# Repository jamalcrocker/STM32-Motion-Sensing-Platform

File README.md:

# STM32 Inertial Sensing PCB

### Custom 4-Layer Embedded Hardware Design | KiCad | STM32L476 | MPU-6050

**Project Status:** In Progress — PCB Design and Layout

## Project Overview

This project focuses on designing a custom four-layer printed circuit board (PCB) that integrates an STM32L476 microcontroller with an MPU-6050 six-axis inertial measurement unit (IMU).

My goal is to develop an embedded system capable of collecting acceleration and angular velocity data through I²C communication. I eventually want to use this board to explore applications involving motion tracking, robotics, and orientation sensing.

Rather than relying on a prebuilt development board, I wanted to take on the challenge of designing the hardware myself, from the circuit schematic to the PCB layout, and eventually bring the design to life through firmware development and physical testing.

## Why I Chose This Project

After working with STM32 microcontrollers in class, I wanted to learn more about the hardware itself instead of just programming it. Through earlier projects, I realized how much I enjoyed PCB design, so I wanted to take on a project where I could design a board of my own.

I've always been fascinated by the technology used in aerospace, especially how aircraft use sensors and electronics to track movement and orientation. That's part of what made me interested in using the MPU-6050.

I saw this project as a chance to combine my interest in aerospace technology with something I enjoy doing, while also improving my skills in PCB design and embedded systems. My goal is to eventually turn this design into a working board that I can program and test.

## Hardware Components

| Component | Purpose |
|---|---|
| STM32L476RGT6 | ARM Cortex-M4 microcontroller |
| MPU-6050 | Six-axis accelerometer and gyroscope |
| I²C Pull-Up Resistors | Support sensor communication |
| Decoupling Capacitors | Support stable power delivery |
| SWD Header | Microcontroller programming and debugging |
| UART Header | Serial communication interface |
| GPIO Expansion Header | Access to additional microcontroller pins |
| Reset Circuit | Manual microcontroller reset |

The board is designed to operate from an external regulated 3.3 V supply.

## PCB Architecture

The PCB uses a four-layer copper stackup:

| Layer | Function |
|---|---|
| Layer 1 — F.Cu | Component placement and signal routing |
| Layer 2 — In1.Cu | Ground plane |
| Layer 3 — In2.Cu | 3.3 V power plane |
| Layer 4 — B.Cu | Additional signal routing |

This configuration provides dedicated power and ground distribution while allowing signal connections to be routed across the outer layers.

## Engineering Design Considerations

### Sensor Communication

The STM32 is designed to communicate with the MPU-6050 through an I²C interface using SDA and SCL connections with external pull-up resistors.

### Power Distribution

The design incorporates dedicated power and ground planes, local decoupling capacitors, and vias to connect components to their respective supply networks.

### Programming and Debugging

An SWD interface provides access to the microcontroller for future firmware programming and debugging.

### Expandability

UART and GPIO headers provide connections for future external devices, testing, and embedded applications.

## Development Progress

- [x] Completed circuit schematic and passed KiCad ERC
- [x] Selected components and assigned footprints
- [x] Configured four-layer PCB with power and ground planes
- [ ] Complete PCB routing and pass DRC
- [ ] Manufacture and assemble the PCB
- [ ] Develop firmware and test sensor communication on the PCB

## Future Development

After completing and validating the PCB layout, my next goal is to manufacture and assemble the board. Since I already have experience programming STM32 microcontrollers in C, I plan to apply those skills to the PCB I designed by developing firmware that communicates with the MPU-6050 through I²C.

Once the board is working, I want to use the accelerometer and gyroscope measurements to create a simple motion-tracking or orientation-monitoring application.

Long term, I'd like to continue exploring how embedded hardware and inertial sensors are used in more advanced systems, particularly robotics and aerospace electronics.

## Tools and Technologies

- **PCB Design:** KiCad
- **Microcontroller:** STM32L476 (ARM Cortex-M4)
- **Sensor:** MPU-6050 IMU
- **Communication:** I²C, UART, SWD
- **Firmware Development:** Embedded C, STM32CubeIDE (planned for this board)

---

*This project is currently in the PCB design stage. The hardware has not yet been manufactured or physically tested.*

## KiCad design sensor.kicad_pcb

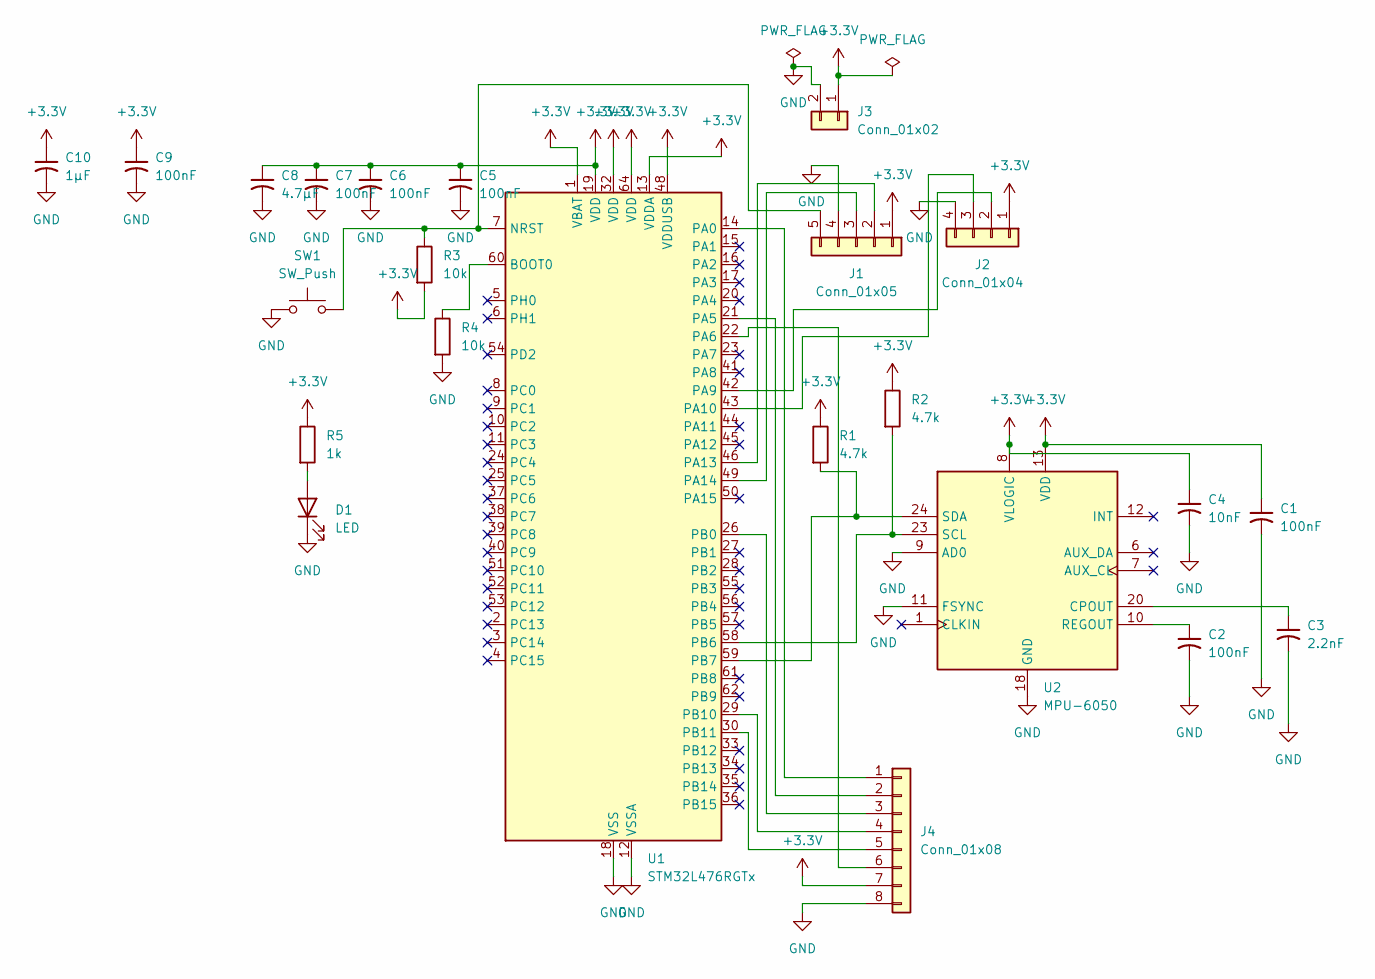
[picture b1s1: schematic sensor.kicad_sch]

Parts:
C1, C2, C5, C6, C7, C9: 100nF; C_0603_1608Metric
C3: 2.2nF; C_0603_1608Metric
C4: 10nF; C_0603_1608Metric
C8: 4.7µF; C_0805_2012Metric
C10: 1μF; C_0805_2012Metric
D1: LED; LED_0603_1608Metric
J1: Conn_01x05; PinHeader_1x05_P2.54mm_Vertical
J2: Conn_01x04; PinHeader_1x04_P2.54mm_Vertical
J3: Conn_01x02; PinHeader_1x02_P2.54mm_Vertical
J4: Conn_01x08; PinHeader_1x08_P2.54mm_Vertical
R1, R2: 4.7k; R_0603_1608Metric
R3, R4: 10k; R_0603_1608Metric
R5: 1k; R_0603_1608Metric
SW1: SW_Push; SW_SPST_PTS645
U1: STM32L476RGTx; LQFP-64_10x10mm_P0.5mm; MPN STM32L476RGT6
U2: MPU-6050; InvenSense_QFN-24_4x4mm_P0.5mm; MPN MPU-6050

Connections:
+3.3V: C1.1, C4.1, C5.1, C6.1, C7.1, C8.1, C9.1, C10.1, J1.1, J2.1, J3.1, J4.7, R1.1, R2.1, R3.2, R5.1, U1.1 (VBAT), U1.13 (VDDA), U1.19 (VDD), U1.32 (VDD), U1.48 (VDDUSB), U1.64 (VDD), U2.8 (VLOGIC), U2.13 (VDD)
GND: C1.2, C2.2, C3.2, C4.2, C5.2, C6.2, C7.2, C8.2, C9.2, C10.2, D1.1 (K), J1.4, J2.4, J3.2, J4.8, R4.2, SW1.1, U1.12 (VSSA), U1.18 (VSS), U1.31 (VSS), U1.47 (VSS), U1.63 (VSS), U2.9 (AD0), U2.11 (FSYNC), U2.18 (GND)
unnamed: D1.2 (A), R5.2
unnamed: J1.2, U1.46 (PA13)
unnamed: J1.3, U1.49 (PA14)
unnamed: J1.5, R3.1, SW1.2, U1.7 (NRST)
unnamed: J2.2, U1.42 (PA9)
unnamed: J2.3, U1.43 (PA10)
unnamed: J4.1, U1.14 (PA0)
unnamed: J4.2, U1.21 (PA5)
unnamed: J4.3, U1.26 (PB0)
unnamed: J4.4, U1.29 (PB10)
unnamed: J4.5, U1.30 (PB11)
unnamed: J4.6, U1.22 (PA6)
unnamed: R4.1, U1.60 (BOOT0)
unnamed: R2.2, U1.58 (PB6), U2.23 (SCL)
unnamed: R1.2, U1.59 (PB7), U2.24 (SDA)
unnamed: C3.1, U2.20 (CPOUT)
unnamed: C2.1, U2.10 (REGOUT)

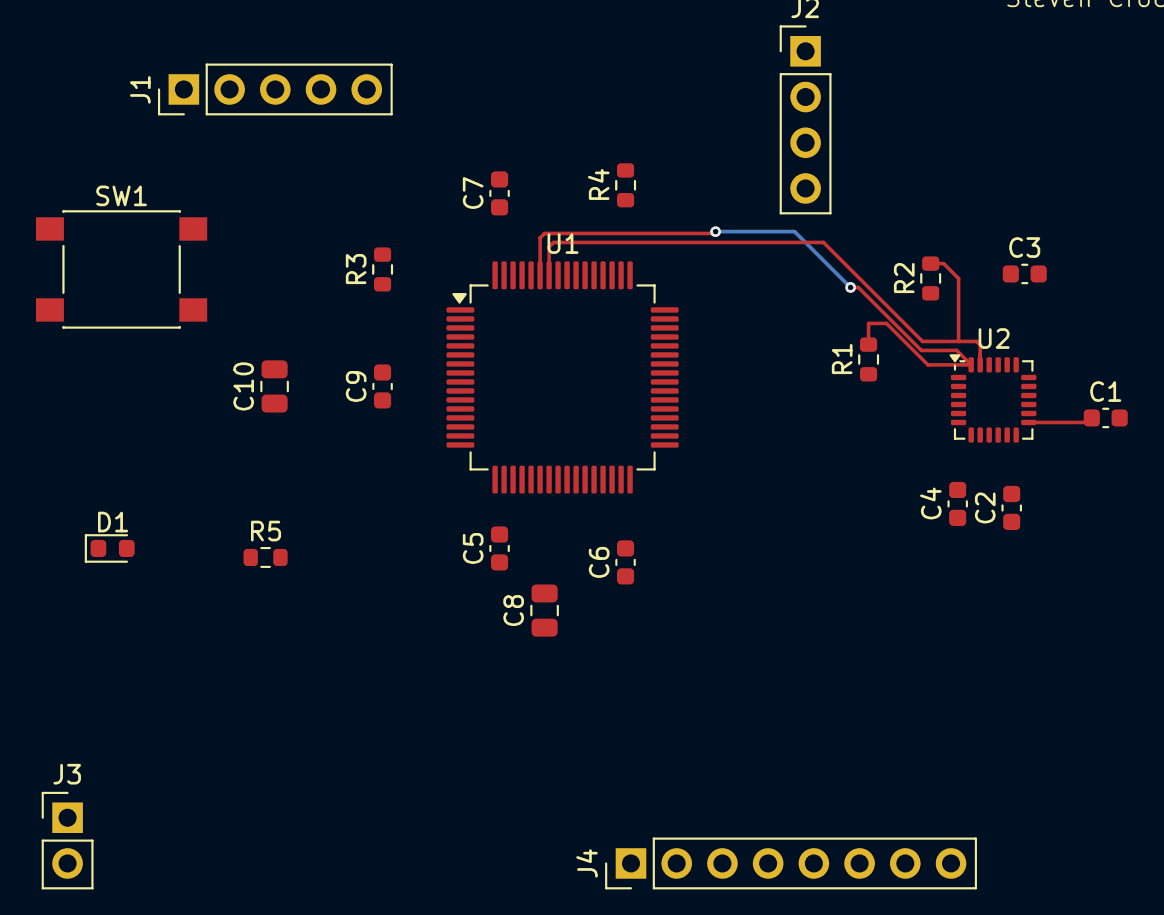
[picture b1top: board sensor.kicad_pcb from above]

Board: 2 copper layers, 23 parts (0 on the bottom side), 19 nets.
